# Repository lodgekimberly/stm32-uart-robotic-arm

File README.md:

# stm32-uart-robotic-arm
STM32-based robotic arm firmware that receives control commands through a USB-to-UART connection and uses PWM signals to control multiple servo motors.

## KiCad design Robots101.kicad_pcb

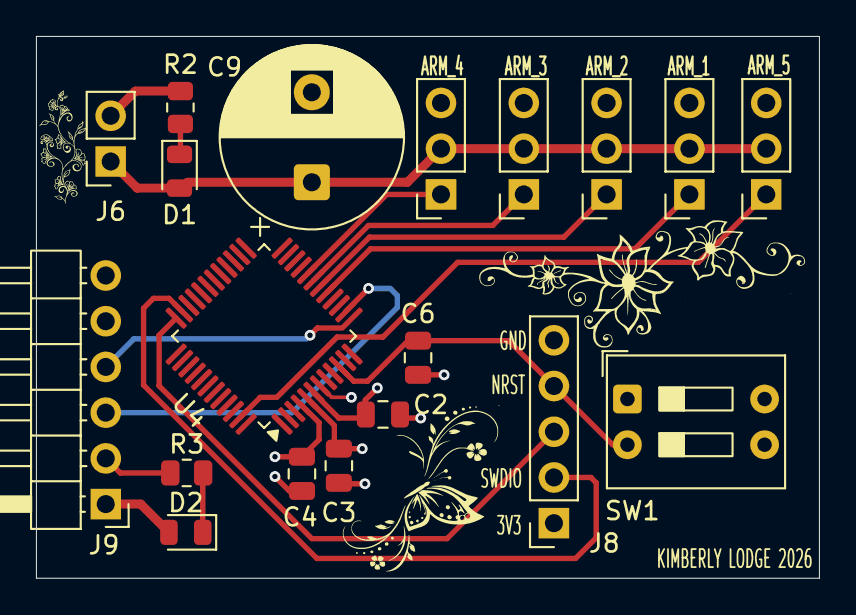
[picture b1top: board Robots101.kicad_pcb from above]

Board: 4 copper layers, 43.5 x 30.1 mm, 19 parts (0 on the bottom side), 15 nets.

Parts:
ARM_1, ARM_2, ARM_3, ARM_4, ARM_5: Conn_01x03; PinSocket_1x03_P2.54mm_Vertical
C2, C3, C6: 100nF; C_0805_2012Metric
C4: 4.7uF; C_0805_2012Metric
C9: 1000uF; CP_Radial_D10.0mm_P5.00mm
D1, D2: LED; D_0805_2012Metric
J6: Conn_01x02; PinSocket_1x02_P2.54mm_Vertical
J8: Conn_01x05; PinSocket_1x05_P2.54mm_Vertical
J9: Conn_01x06; PinHeader_1x06_P2.54mm_Horizontal
R2, R3: 1K; R_0805_2012Metric
SW1: SW_Push; SW_DIP_SPSTx02_Slide_9.78x7.26mm_W7.62mm_P2.54mm
U4: STM32G030C8T; LQFP-48_7x7mm_P0.5mm

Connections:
+3V3: C2.1, C3.1, C4.1, D2.2 (A), J8.1, J9.1, U4.4 (VBAT), U4.5 (VREF+), U4.6 (VDD)
ARM_1: ARM_1.1, U4.17 (PA6)
ARM_2: ARM_2.1, U4.18 (PA7)
ARM_3: ARM_3.1, U4.19 (PB0)
ARM_4: ARM_4.1, U4.20 (PB1)
ARM_5: ARM_5.1, U4.47 (PB8)
GND: ARM_1.3, ARM_2.3, ARM_3.3, ARM_4.3, ARM_5.3, C2.2, C3.2, C4.2, C6.2, C9.2, J6.2, J8.5, J9.2, R2.2, R3.2, SW1.1, U4.7 (VSS)
NRST: C6.1, J8.4, SW1.2, U4.10 (NRST)
unnamed: D1.1 (K), R2.1
unnamed: D2.1 (K), R3.1
SWCLK: J8.3, U4.36 (PA14)
SWDIO: J8.2, U4.35 (PA13)
USART2_RX: J9.3, U4.14 (PA3)
USART2_TX: J9.4, U4.13 (PA2)
V_ARM: ARM_1.2, ARM_2.2, ARM_3.2, ARM_4.2, ARM_5.2, C9.1, D1.2 (A), J6.1
